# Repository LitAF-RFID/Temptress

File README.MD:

# LitAF Temptress
This device is a miniaturised NFC tag that enables the reading of temperature from two TMP112 sensors as well as a LED that can be enabled or disabled. The NFC interface is provided by an NTAG5 NFC to I2C bridge chip.

## Coil Design
-   **Target Frequency:** 13.56MHz
-   **Target Q Factor:** 50
-   **Chip Capacitance:** 15pf
-   **External Capacitance:** ~62pf
-   **Target Coil Inductance:** 1.76uH
-   **Coil Shape:** "Rectangular"
-   **Coil Height:** 25mm
-   **Coil Width:** 5mm
-   **Coil Turns:** 8
-   **Coil Trace Width:** 0.1mm
-   **Coil Trace Spacing:** 0.1mm
-   **Coil Copper Thickness:** 2oz

## Bill Of Materials
-   1 x NTAG5 (Link or Boost)
-   2 x TMP117
-   3 x Tuning Cap (C1-3)
-   3 x Smoothing Cap (C4-C6)
-   1 x Current Limiting Resistor
-   1 x IN-S124AR LED

## Schematic

## Note
This was designed as a demo project for a class that I ran. The design has not been tested and was made in a very short period of time. Whilst it should work, it is far from the ideal design for this sort of device.

## Manufacturing Info
This design was created with the PCBWay 2 layer flex PCB manufacturing specifications in mind. If you order this using the CAM files provided, you need to order with 2oz copper.

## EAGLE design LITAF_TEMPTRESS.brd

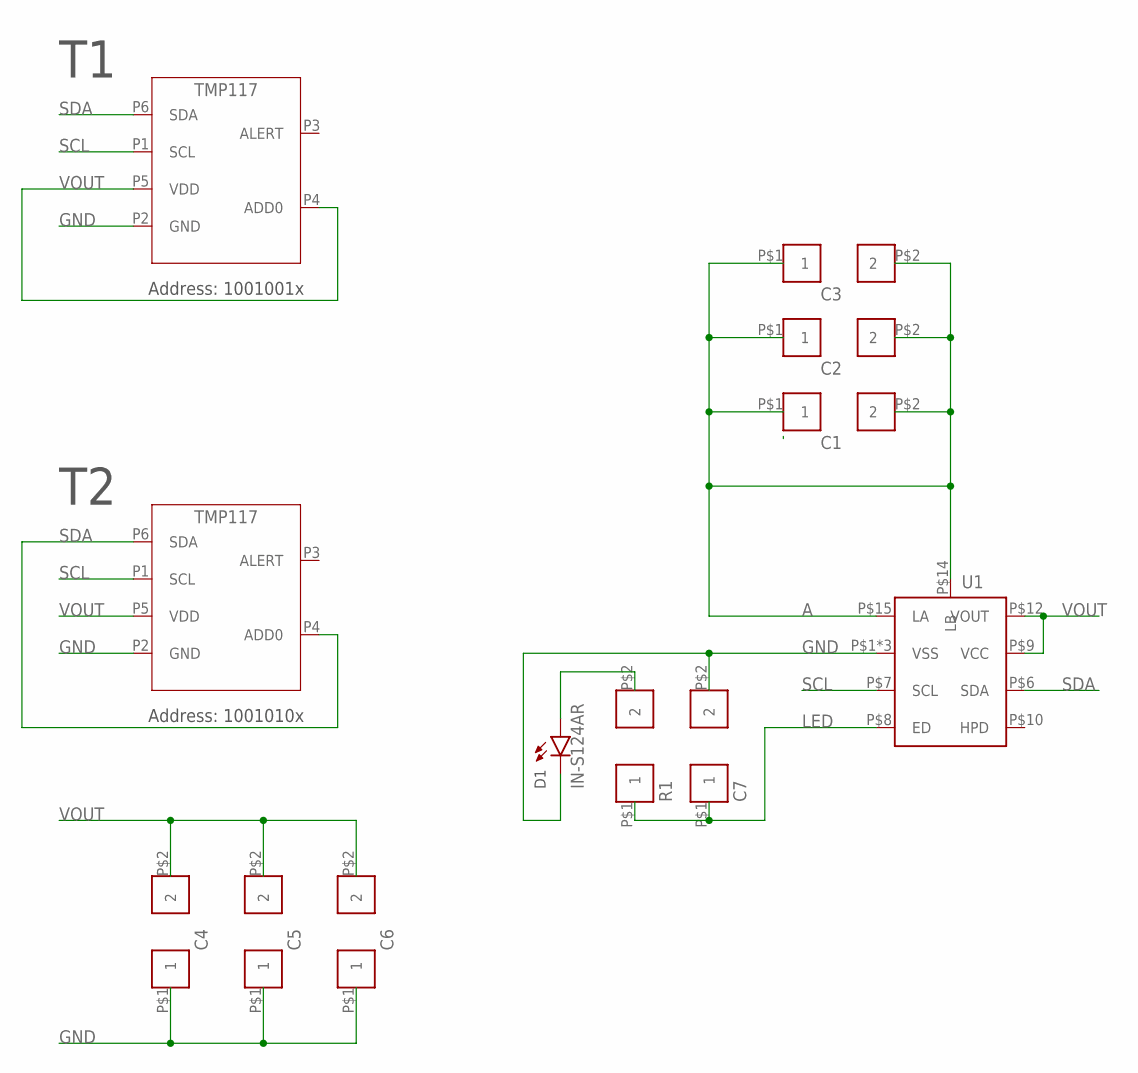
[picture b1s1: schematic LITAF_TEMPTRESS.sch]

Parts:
C1, C2, C3, C5, C6, C7: 0402-CAP; 0402-SMT
C4: 0603-CAP; 0603-SMT[WIDE]
D1: IN-S124AR
R1: 0402-CAP; 0402-SMT
T1, T2: TMP117; DRV0006B
U1: NTAG5_LINK_NTP53X2; SOT1161-2

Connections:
A: C1.P$1 (1), C1.P$2 (2), C2.P$1 (1), C2.P$2 (2), C3.P$1 (1), C3.P$2 (2), U1.P$14 (LB), U1.P$15 (LA)
GND: C4.P$1 (1), C5.P$1 (1), C6.P$1 (1), C7.P$2 (2), D1.P$2 (C), T1.P2 (GND), T2.P2 (GND), U1.P$1 (VSS), U1.P$2 (VSS), U1.P$11 (VSS)
LED: C7.P$1 (1), R1.P$1 (1), U1.P$8 (ED)
unnamed: D1.P$1 (A), R1.P$2 (2)
SCL: T1.P1 (SCL), T2.P1 (SCL), U1.P$7 (SCL)
SDA: T1.P6 (SDA), T2.P4 (ADD0), T2.P6 (SDA), U1.P$6 (SDA)
VOUT: C4.P$2 (2), C5.P$2 (2), C6.P$2 (2), T1.P4 (ADD0), T1.P5 (VDD), T2.P5 (VDD), U1.P$9 (VCC), U1.P$12 (VOUT)

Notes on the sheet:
Address: 1001001x
Address: 1001010x

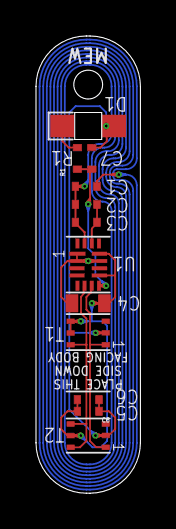
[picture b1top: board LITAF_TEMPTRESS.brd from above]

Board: 2 copper layers, 5.8 x 25.4 mm, 12 parts (0 on the bottom side), 7 nets.

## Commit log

2024-04-04 Initial Design
    This has not been peer reviewed or tested, this is just the initial prototype design
2024-04-05 Added current limiting resistor for LED
